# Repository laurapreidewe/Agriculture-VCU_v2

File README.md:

# Agricultural VCU V2

Vehicle control unit PCB for agricultural robots and machinery, built around the Nuvoton M467HJHAN microcontroller. V2 provides Ethernet, CAN, UART, ADC/DAC, PWM, and six relay channels.

The project was originally designed in **KiCad 8** and has been updated to **KiCad 10**. The current schematic and PCB files identify KiCad 10.0 as their generator.

**Known issue:** the relay circuit requires rework because pins **3 and 4** are swapped in the optocoupler footprint. Refer to the [PCB Test Report Rev. A](docs/references/pcb-test-report-rev-a.pdf) for rework details.

## Board overview

The photograph shows the assembled board with relay rework wiring.

## Hardware

| Item | V2 design |
| --- | --- |
| MCU | Nuvoton M467HJHAN, Arm Cortex-M4, LQFP176 |
| Power | 12 V input, external 12 V to 5 V buck module, TPS79533 3.3 V regulator |
| Input protection | Fuse, power switch, and unidirectional TVS diode |
| Ethernet | RTL8201FI PHY, RMII connection to the MCU, magnetics, and RJ45 connector |
| CAN | Two interfaces using external MCP2551 transceiver modules |
| UART | UART0 and UART2 connectors |
| Analogue interfaces | Two ADC inputs with 5 V to 3.3 V scaling and two DAC output channels |
| PWM | Two outputs, BPWM0_CH0 and BPWM1_CH0, with BSS138 level shifting |
| Relays | Six 12 V SPDT channels with optocoupler-based drivers; rework required |
| Expansion and debug | Four 2×20 GPIO sockets and a Nu-Link SWD header |
| Storage | External SPI flash; the V1 SD-card module connector was removed |
| PCB | Four layers, 176.53 × 184.15 mm, 2 mm thick |
| Fabrication limits | 0.1 mm minimum track width/spacing and 0.2 mm minimum hole diameter |

Connector pinouts, switches, LEDs, and test points are listed in the [user manual](docs/references/user-manual.pdf).

## Project files and KiCad setup

Open [UGV Control Unit.kicad_pro](UGV%20Control%20Unit.kicad_pro) with KiCad 10 to work with the current project.

| File | Contents |
| --- | --- |
| [UGV Control Unit.kicad_sch](UGV%20Control%20Unit.kicad_sch) | Root schematic |
| [UGVPower.kicad_sch](UGVPower.kicad_sch) | Power supply |
| [UGVMCU.kicad_sch](UGVMCU.kicad_sch) | MCU, clocks, debug, USB, and flash |
| [UGVGPIO.kicad_sch](UGVGPIO.kicad_sch) | Relays and external interfaces |
| [UGVEthernet.kicad_sch](UGVEthernet.kicad_sch) | Ethernet circuitry |
| [UGV Control Unit.kicad_pcb](UGV%20Control%20Unit.kicad_pcb) | PCB layout |
| [bom/ibom.html](bom/ibom.html) | Interactive BOM and component placement |
| [UGVPCBGerber.zip](UGVPCBGerber.zip) | Existing Gerbers and manufacturing data |
| [UGV Control Unit-odb.zip](UGV%20Control%20Unit-odb.zip) | Existing ODB++ export |
| [Top placement](UGV%20Control%20Unit-top.pos) / [bottom placement](UGV%20Control%20Unit-bottom.pos) | Component position files |
| [3D model.zip](3D%20model.zip) | Complete board STEP model |

The design references custom symbol/footprint libraries, including `MCU_Nuvoton_M467`, `TPS79533DCQ`, and `DESD5V0U1BA_7`. Configure the required libraries when editing or updating components. Some PCB 3D-model paths still use `${KICAD8_3DMODEL_DIR}`; check those paths in KiCad 10 if individual component models are missing. The STEP archive contains the complete board model.

## Changes from V1 to V2

The [Version Control Report](docs/references/version-control-report.pdf) documents the hardware changes from V1 (February 2025) to V2 (January 2026). This hardware revision history is separate from the KiCad 8-to-10 software migration.

| Area | V1 | V2 |
| --- | --- | --- |
| MCU | STM32F446RE, LQFP64 | Nuvoton M467HJHAN, LQFP176 |
| Clocks | 8.192 MHz external crystal; external RTC clock unused | 12 MHz external crystal and external RTC clock |
| Power input | Four-pin connector for 12 V, 72 V, and grounds | Two-pin 12 V/GND connector; added TVS protection |
| MCU supply | VCAP routing mistake required a manual trace cut | LDO_CAP pins kept separate from the 3.3 V rail |
| Decoupling | 0402 capacitors | 0603 capacitors |
| GPIO expansion | One 2×13 and three 2×12 sockets, with 3.3 V and 5 V power pins | Four 2×20 sockets, with 3.3 V power pins |
| Debug | STM32 SWD and boot-jumper circuitry | M467 SWD on PF.0/PF.1 with external pull-ups; simplified boot circuitry |
| Ethernet | Unused | Added PHY, magnetics, and RJ45 interface |
| Relays | 12 relays, BJT-based drivers, D-sub/terminal-block connections | Six SPDT relays, optocoupler-based drivers, individual terminal blocks |
| Interfaces | ADC, DAC, CAN, one UART, and SD-card module connector | Retained ADC/DAC/CAN; two UARTs and two PWM outputs; removed SD-card module connector |
| Storage and USB | No external flash; USB shield directly grounded | Added SPI flash; USB shield connected through a ferrite bead |
| Layout | 180 × 180 mm; components on the top layer | 176.53 × 184.15 mm; some Ethernet components on the bottom layer, edge connectors, and teardrops at small vias |

## Reference documents

| Source | Purpose |
| --- | --- |
| [Presentation1.pptx](docs/references/Presentation1.pptx) | Original annotated board overview, rendered above as a PNG |
| [Agricultural VCU V2 User Manual](docs/references/user-manual.pdf) | Pin assignments, connectors, switches, LEDs, test points, and schematics |
| [Agricultural VCU V2 Testing Protocol](docs/references/testing-protocol.pdf) | Assembly and laboratory test procedures |
| [Agricultural VCU v2 PCB Test Report Rev. A](docs/references/pcb-test-report-rev-a.pdf) | PCB test record and relay rework details |
| [Agricultural VCU V2 Version Control Report](docs/references/version-control-report.pdf) | Changes from hardware V1 to V2 |
| [20260810_Rai.pptx](docs/references/20260810_Rai.pptx) | V2 evaluation list; original location: `season 2/projects/presentation/20260810_Rai.pptx` |

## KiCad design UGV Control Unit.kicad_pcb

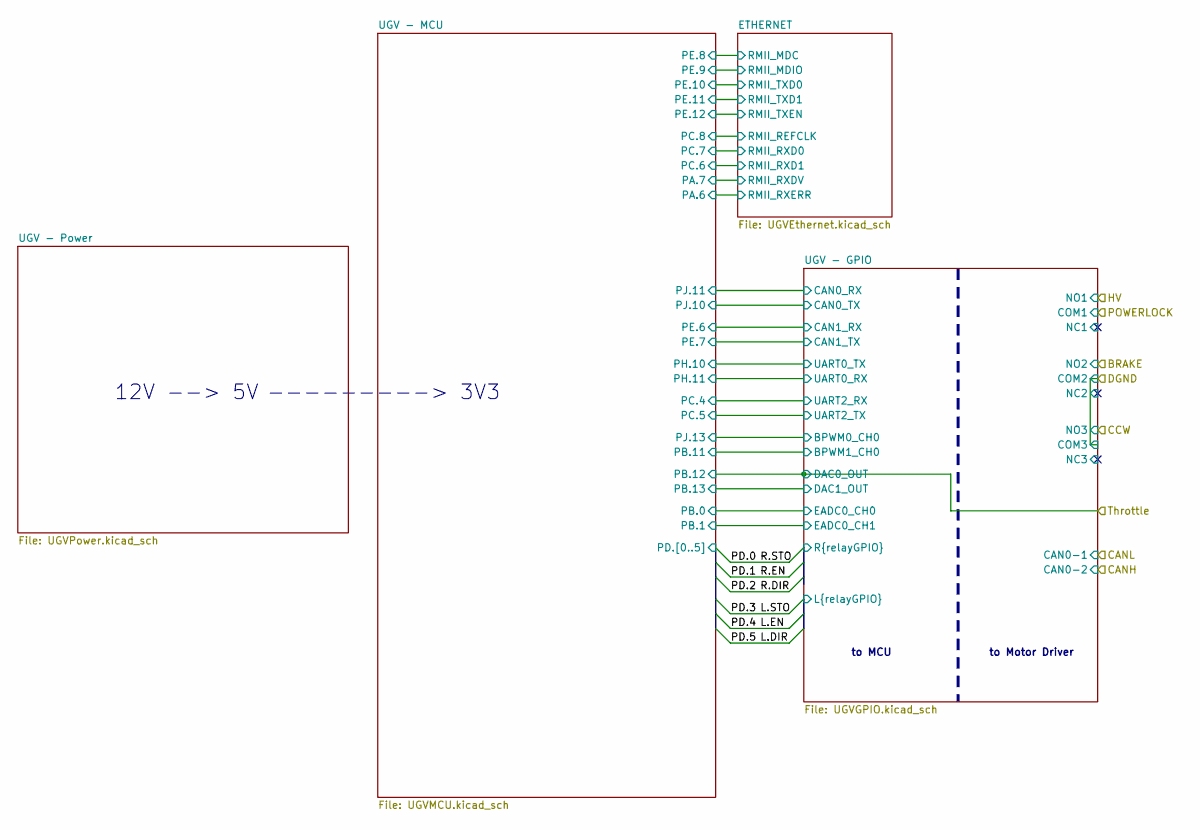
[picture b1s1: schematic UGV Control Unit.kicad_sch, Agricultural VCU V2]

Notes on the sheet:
to MCU
to Motor Driver
12V --> 5V
---------> 3V3

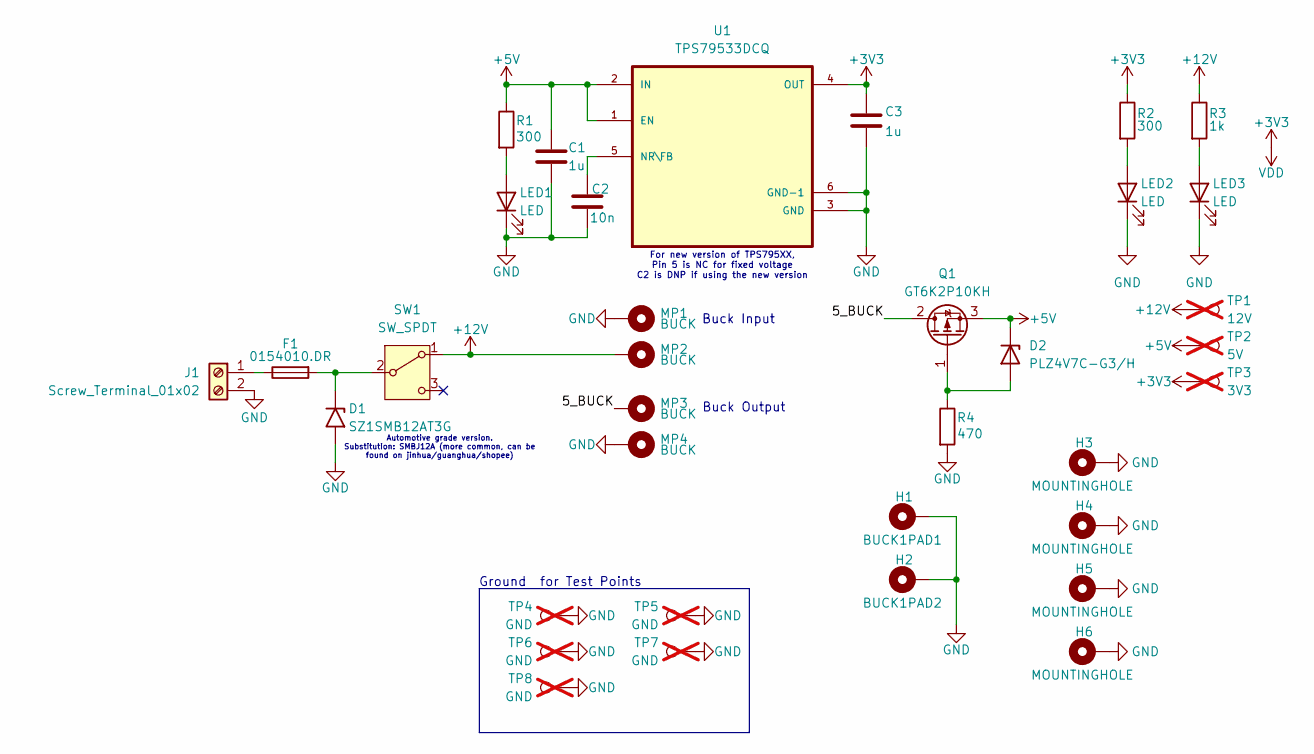
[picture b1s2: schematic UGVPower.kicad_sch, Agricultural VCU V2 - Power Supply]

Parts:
C1, C3: 1u; C_0603_1608Metric_Pad1.08x0.95mm_HandSolder; MANUFACTURER_PART_NUMBER 0603YC105JAT2A
C2: 10n; C_0603_1608Metric_Pad1.08x0.95mm_HandSolder; MANUFACTURER_PART_NUMBER KGM15AR51E103KT
D1: SZ1SMB12AT3G; D_SMB_Handsoldering; MANUFACTURER_PART_NUMBER SZ1SMB12AT3G
D2: PLZ4V7C-G3/H; CR_PLZ5V1C_VIS-L; MANUFACTURER_PART_NUMBER PLZ4V7C
F1: 0154010.DR; Fuseholder_Littelfuse_Nano2_154x; MANUFACTURER_PART_NUMBER 0154010.DR
H1: BUCK1PAD1; MountingHole_3.2mm_M3_Pad_TopBottom
H2: BUCK1PAD2; MountingHole_3.2mm_M3_Pad_TopBottom
H3, H4, H5, H6: MOUNTINGHOLE; MountingHole_3.2mm_M3_Pad_Via
J1: Screw_Terminal_01x02; TerminalBlock_TE_NC6-P107-02_1x02_P9.53mm; MANUFACTURER_PART_NUMBER 1437664-4
LED1, LED2, LED3: LED; LED_0603_1608Metric_Pad1.05x0.95mm_HandSolder; MANUFACTURER_PART_NUMBER 150060SS75003
MP1, MP2, MP3, MP4: BUCK; MountingHole_4.3mm_M4_Pad_TopBottom; MANUFACTURER_PART_NUMBER 24885
Q1: GT6K2P10KH; TO-252-2; MANUFACTURER_PART_NUMBER GT6K2P10KH
R1, R2: 300; R_0603_1608Metric_Pad0.98x0.95mm_HandSolder; MANUFACTURER_PART_NUMBER RT0603BRD07300RL
R3: 1k; R_0603_1608Metric_Pad0.98x0.95mm_HandSolder; MANUFACTURER_PART_NUMBER RT0603FRE131KL
R4: 470; R_0603_1608Metric_Pad0.98x0.95mm_HandSolder; MANUFACTURER_PART_NUMBER RT0603FRE07470RL
SW1: SW_SPDT; SW_500SSP1S1M2REA; MANUFACTURER_PART_NUMBER 500SSP1S1M2REA
TP1: 12V; TestPoint_Pad_D1.0mm; not fitted
TP2: 5V; TestPoint_Pad_D1.0mm; not fitted
TP3: 3V3; TestPoint_Pad_D1.0mm; not fitted
TP4, TP5, TP6, TP7, TP8: GND; PinHeader_1x01_P2.54mm_Vertical; not fitted
U1: TPS79533DCQ; SOT127P706X180-6N; MANUFACTURER_PART_NUMBER TPS79533DCQ

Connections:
+12V: MP2.1, R3.1, SW1.1 (A), TP1.1; also elsewhere on the board
/UGV - Power/5_BUCK: MP3.1, Q1.2 (D)
GND: C1.2, C2.2, C3.2, D1.2 (A2), H1.1, H2.1, H3.1, H4.1, H5.1, H6.1, J1.2, LED1.1 (K), LED2.1 (K), LED3.1 (K), MP1.1, MP4.1, R4.2, TP4.1, TP5.1, TP6.1, TP7.1, TP8.1, U1.3 (GND), U1.6 (GND-1); also elsewhere on the board
unnamed: D1.1 (A1), F1.2, SW1.2 (B)
unnamed: D2.2 (A), Q1.1 (G), R4.1
unnamed: F1.1, J1.1
unnamed: LED1.2 (A), R1.2
unnamed: LED2.2 (A), R2.2
unnamed: LED3.2 (A), R3.2
unnamed: C2.1, U1.5 (NR\FB)

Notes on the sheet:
Automotive grade version. Substitution: SMBJ12A (more common, can be found on jinhua/guanghua/shopee)
Ground for Test Points
Buck Input
For new version of TPS795XX, Pin 5 is NC for fixed voltage C2 is DNP if using the new version
Buck Output

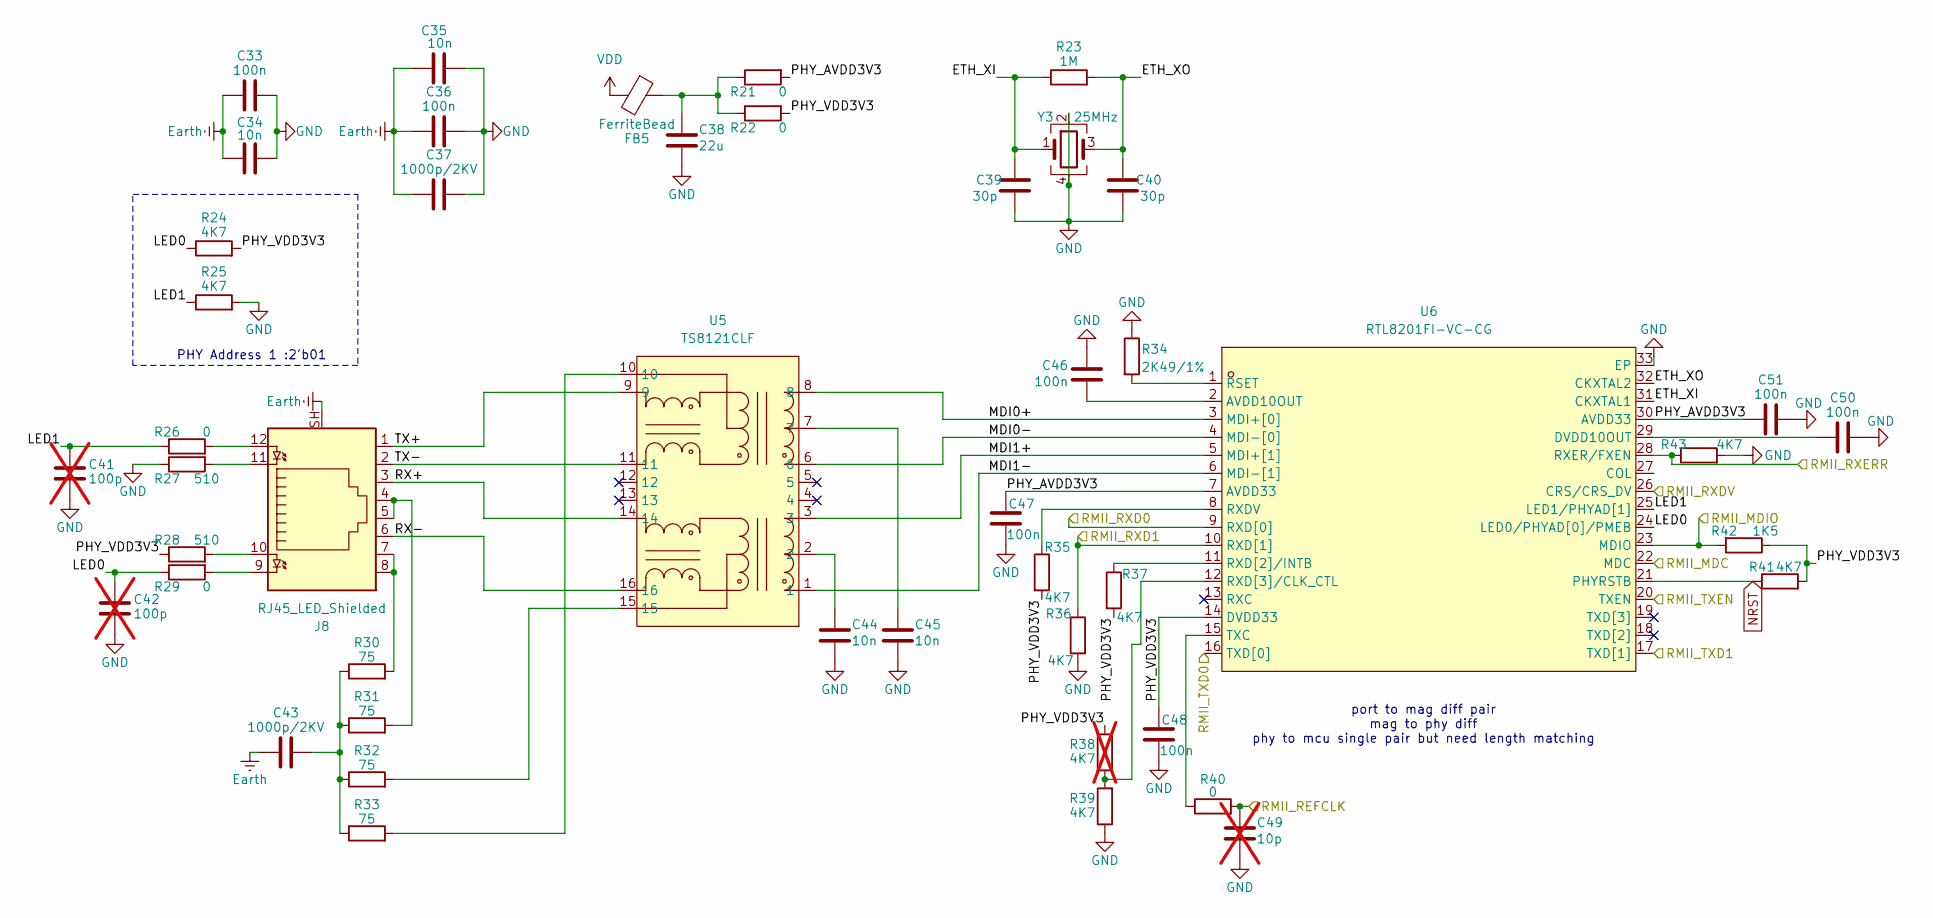
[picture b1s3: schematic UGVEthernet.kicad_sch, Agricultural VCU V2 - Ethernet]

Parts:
C33, C36, C46, C47, C48, C50, C51: 100n; C_0603_1608Metric_Pad1.08x0.95mm_HandSolder; MANUFACTURER_PART_NUMBER KGM15BR71H104KT
C34, C35, C44, C45: 10n; C_0603_1608Metric_Pad1.08x0.95mm_HandSolder; MANUFACTURER_PART_NUMBER KGM15AR51E103KT
C37, C43: 1000p/2KV; C_1206_3216Metric_Pad1.33x1.80mm_HandSolder; MANUFACTURER_PART_NUMBER CC1206JKX7RDBB102
C38: 22u; C_0603_1608Metric_Pad1.08x0.95mm_HandSolder; MANUFACTURER_PART_NUMBER GRM188R61A226ME15D
C39, C40: 30p; C_0603_1608Metric_Pad1.08x0.95mm_HandSolder; MANUFACTURER_PART_NUMBER 06035A300JAT2A
C41, C42: 100p; C_0603_1608Metric_Pad1.08x0.95mm_HandSolder; MANUFACTURER_PART_NUMBER KGM15ACG1H101FT; not fitted
C49: 10p; C_0603_1608Metric_Pad1.08x0.95mm_HandSolder; MANUFACTURER_PART_NUMBER CC0603JRNPO9BN100; not fitted
FB5: FerriteBead; L_0603_1608Metric_Pad1.05x0.95mm_HandSolder; MANUFACTURER_PART_NUMBER BLM18KG300TN1D
J8: RJ45_LED_Shielded; RJ45_Amphenol_RJHSE538X; MANUFACTURER_PART_NUMBER RJHSE5381
R21, R22, R26, R29, R40: 0; R_0603_1608Metric_Pad0.98x0.95mm_HandSolder; MANUFACTURER_PART_NUMBER RC0603JR-070RL
R23: 1M; R_0603_1608Metric_Pad0.98x0.95mm_HandSolder; MANUFACTURER_PART_NUMBER RC0603FR-101ML
R24, R25, R35, R36, R37, R39, R41, R43: 4K7; R_0603_1608Metric_Pad0.98x0.95mm_HandSolder; MANUFACTURER_PART_NUMBER RC0603FR-134K7L
R27, R28: 510; R_0603_1608Metric_Pad0.98x0.95mm_HandSolder; MANUFACTURER_PART_NUMBER RT0603BRD07510RL
R30, R31, R32, R33: 75; R_0603_1608Metric_Pad0.98x0.95mm_HandSolder; MANUFACTURER_PART_NUMBER RC0603FR-0775RL
R34: 2K49/1%; R_0603_1608Metric_Pad0.98x0.95mm_HandSolder; MANUFACTURER_PART_NUMBER RC0603FR-072K49L
R38: 4K7; R_0603_1608Metric_Pad0.98x0.95mm_HandSolder; MANUFACTURER_PART_NUMBER RC0603FR-134K7L; not fitted
R42: 1K5; R_0603_1608Metric_Pad0.98x0.95mm_HandSolder; MANUFACTURER_PART_NUMBER RT0603FRE071K5L
U5: TS8121CLF; SOP-16_7.0x13.0mm_P1.27mm; MANUFACTURER_PART_NUMBER TS8121CLF; LCSC Part C2839017
U6: RTL8201FI-VC-CG; QFN-32-1EP_5x5mm_P0.5mm_EP3.3x3.3mm_ThermalVias; MANUFACTURER_PART_NUMBER RTL8201FI-VC-CG; LCSC Part C2763557
Y3: 25MHz; Crystal_SMD_SeikoEpson_TSX3225-4Pin_3.2x2.5mm_HandSoldering; MANUFACTURER_PART_NUMBER TSX-3225 25.0000MF10P-C0

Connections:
/ETHERNET/ETH_XI: C39.1, R23.1, U6.31 (CKXTAL1), Y3.1
/ETHERNET/ETH_XO: C40.1, R23.2, U6.32 (CKXTAL2), Y3.3
/ETHERNET/LED0: C42.1, R24.1, R29.1, U6.24 (LED0/PHYAD[0]/PMEB)
/ETHERNET/LED1: C41.1, R25.1, R26.1, U6.25 (LED1/PHYAD[1])
/ETHERNET/MDI0+: U5.8, U6.3 (MDI+[0])
/ETHERNET/MDI0-: U5.6, U6.4 (MDI-[0])
/ETHERNET/MDI1+: U5.3, U6.5 (MDI+[1])
/ETHERNET/MDI1-: U5.1, U6.6 (MDI-[1])
/ETHERNET/PHY_AVDD3V3: C47.1, C51.2, R21.2, U6.7 (AVDD33), U6.30 (AVDD33)
/ETHERNET/PHY_VDD3V3: C48.1, R22.2, R24.2, R28.1, R35.2, R37.2, R38.2, R41.2, R42.1, U6.14 (DVDD33)
/ETHERNET/RX+: J8.3, U5.14
/ETHERNET/RX-: J8.6, U5.16
/ETHERNET/TX+: J8.1, U5.9
/ETHERNET/TX-: J8.2, U5.11
/UGV - MCU/PA.6: R43.1, U6.28 (RXER/FXEN); also elsewhere on the board
/UGV - MCU/PA.7: U6.26 (CRS/CRS_DV); also elsewhere on the board
/UGV - MCU/PC.6: R36.1, U6.10 (RXD[1]); also elsewhere on the board
/UGV - MCU/PC.7: U6.9 (RXD[0]); also elsewhere on the board
/UGV - MCU/PC.8: C49.1, R40.2; also elsewhere on the board
/UGV - MCU/PE.8: U6.22 (MDC); also elsewhere on the board
/UGV - MCU/PE.9: R42.2, U6.23 (MDIO); also elsewhere on the board
/UGV - MCU/PE.10: U6.16 (TXD[0]); also elsewhere on the board
/UGV - MCU/PE.11: U6.17 (TXD[1]); also elsewhere on the board
/UGV - MCU/PE.12: U6.20 (TXEN); also elsewhere on the board
Earth: C33.1, C34.2, C35.1, C36.2, C37.1, C43.1, J8.SH
GND: C33.2, C34.1, C35.2, C36.1, C37.2, C38.2, C39.2, C40.2, C41.2, C42.2, C44.2, C45.2, C46.1, C47.2, C48.2, C49.2, C50.1, C51.1, R25.2, R27.1, R34.1, R36.2, R39.1, R43.2, U6.33 (EP), Y3.2, Y3.4; also elsewhere on the board
NRST: R41.1, U6.21 (PHYRSTB); also elsewhere on the board
unnamed: C38.1, FB5.1, R21.1, R22.1
unnamed: C43.2, R30.1, R31.1, R32.1, R33.1
unnamed: C44.1, U5.2
unnamed: C45.1, U5.7
unnamed: J8.4, J8.5, R31.2
unnamed: J8.7, J8.8, R30.2
unnamed: J8.9, R29.2
unnamed: J8.10, R28.2
unnamed: J8.11, R27.2
unnamed: J8.12, R26.2
unnamed: R32.2, U5.15
unnamed: R33.2, U5.10
unnamed: C46.2, U6.2 (AVDD10OUT)
unnamed: C50.2, U6.29 (DVDD10OUT)
unnamed: R34.2, U6.1 (RSET)
unnamed: R35.1, U6.8 (RXDV)
unnamed: R37.1, U6.11 (RXD[2]/INTB)
unnamed: R38.1, R39.2, U6.12 (RXD[3]/CLK_CTL)
unnamed: R40.1, U6.15 (TXC)

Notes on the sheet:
port to mag diff pair mag to phy diff phy to mcu single pair but need length matching
PHY Address 1 :2'b01

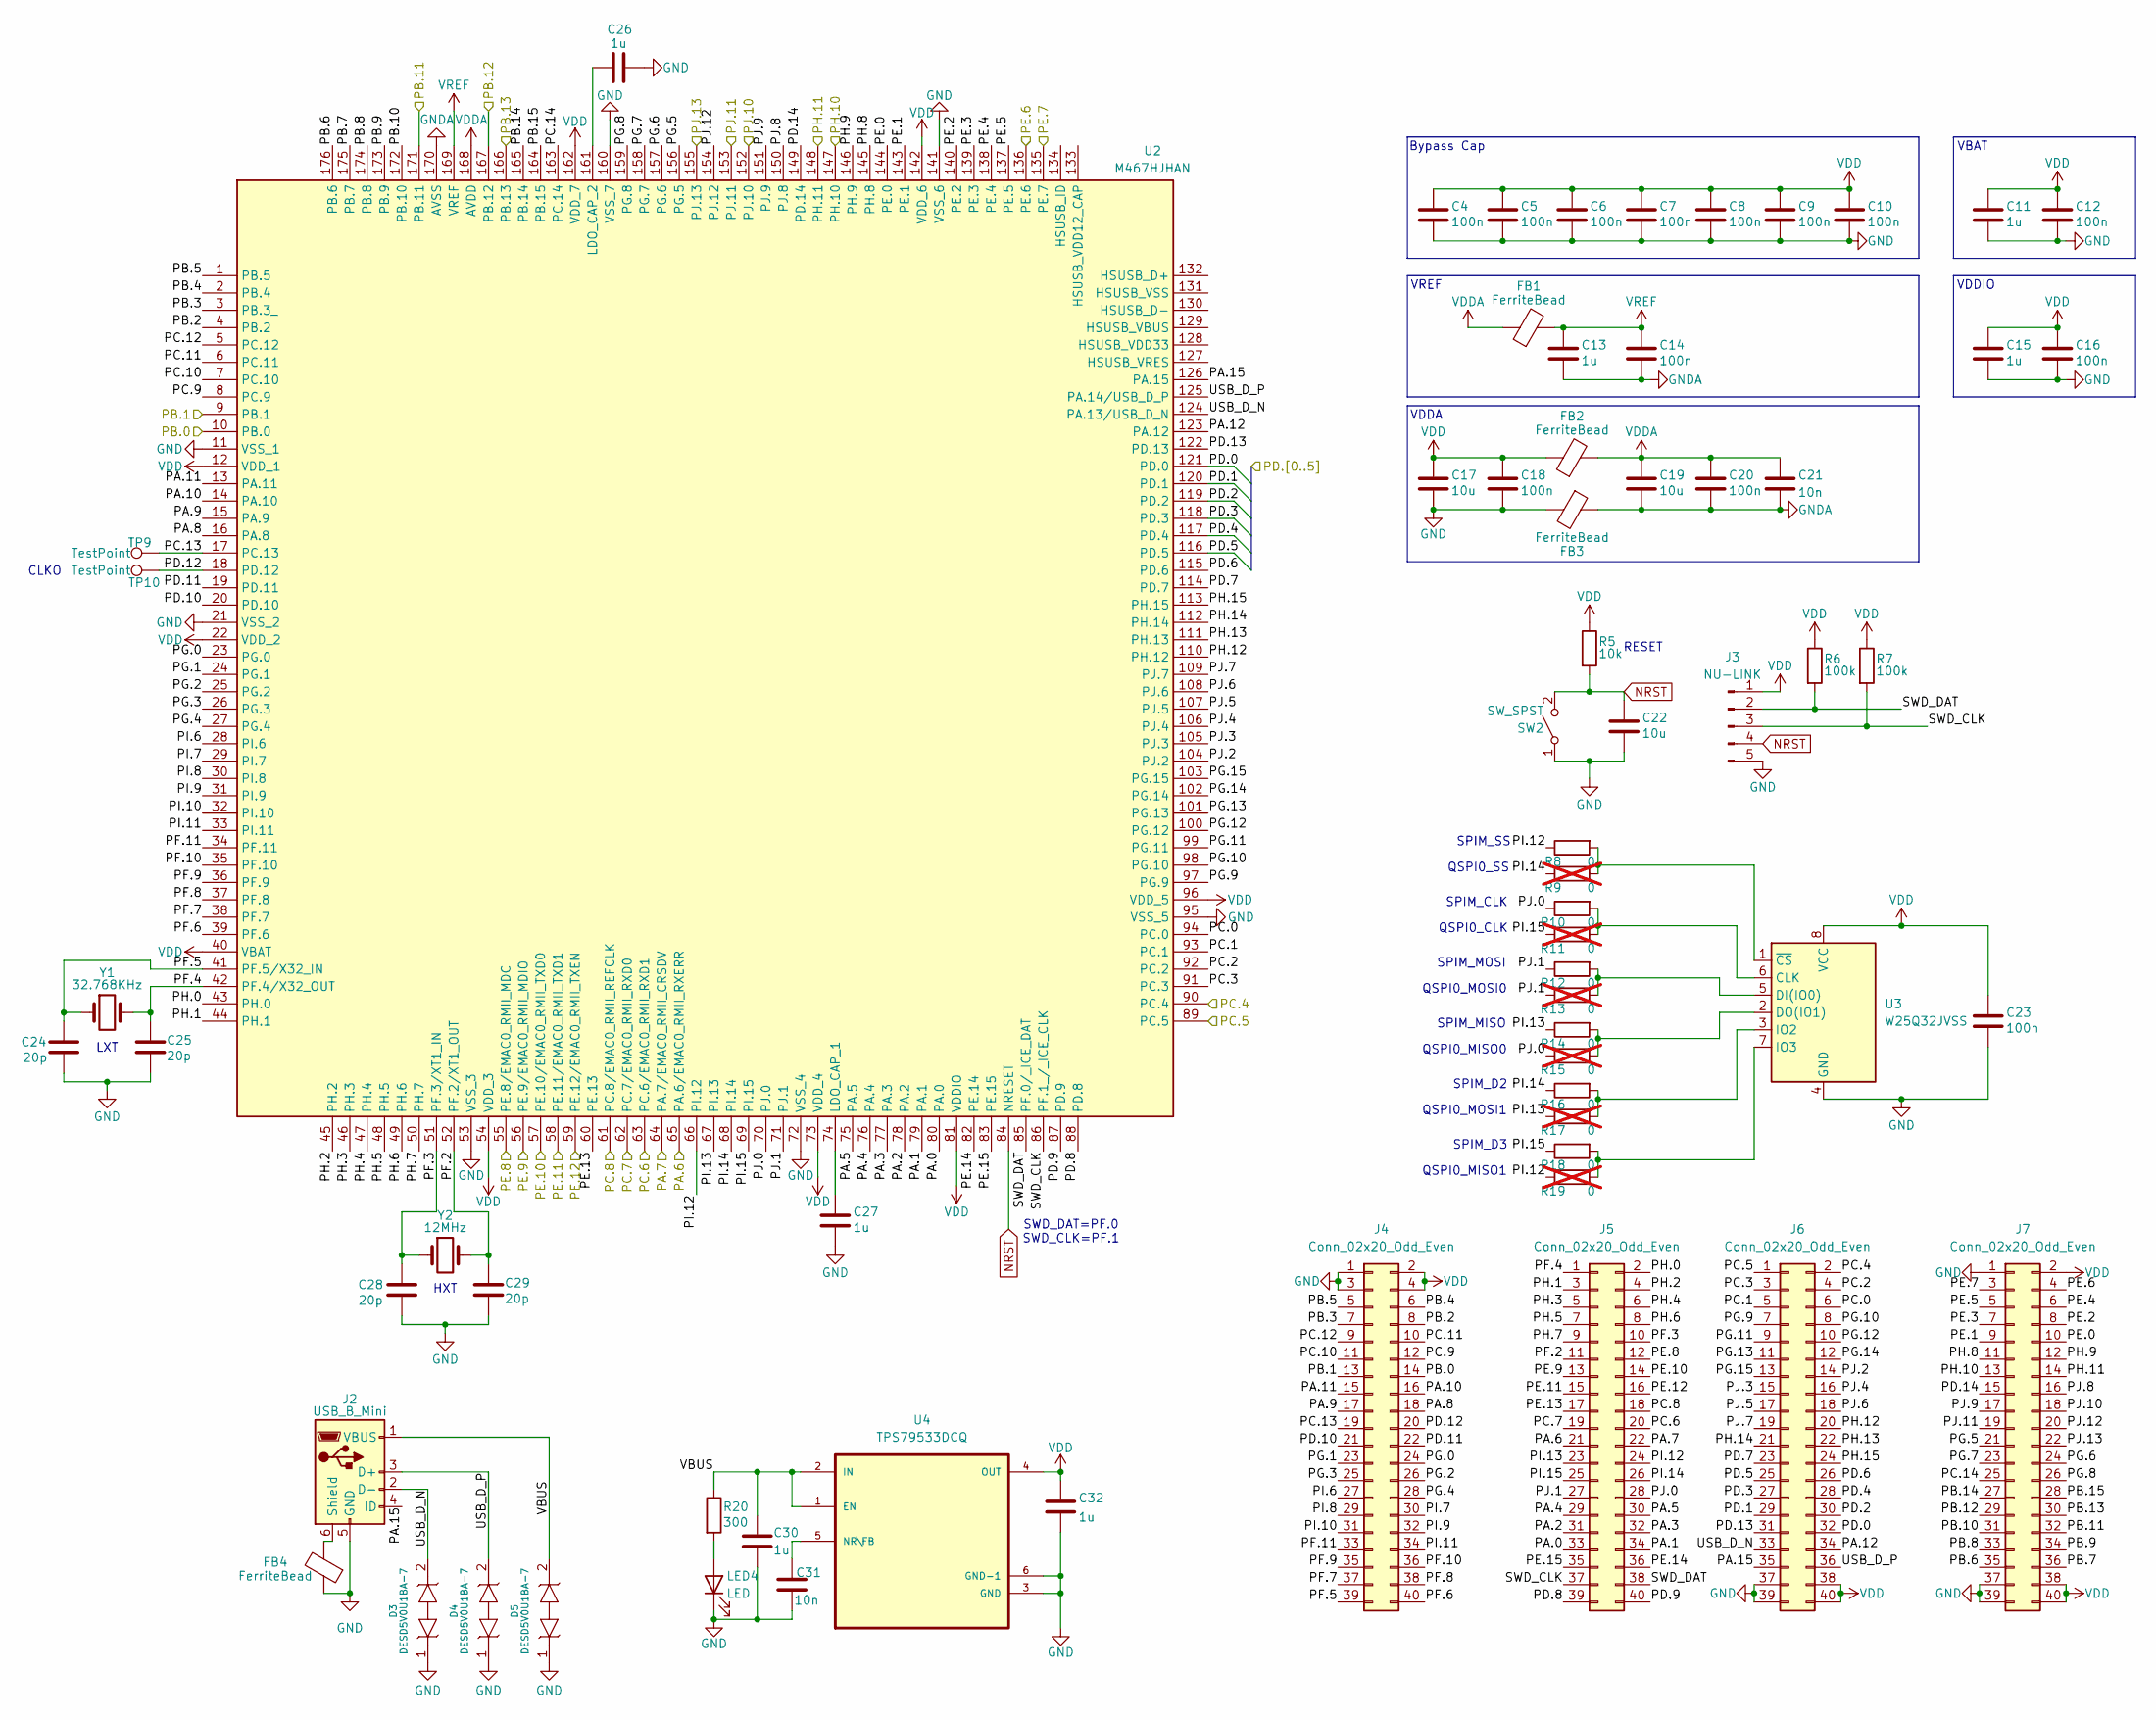
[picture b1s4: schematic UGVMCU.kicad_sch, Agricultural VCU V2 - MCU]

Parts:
C4, C5, C6, C7, C8, C9, C10, C12, C14, C16, C18, C20, C23: 100n; C_0603_1608Metric_Pad1.08x0.95mm_HandSolder; MANUFACTURER_PART_NUMBER KGM15BR71H104KT
C11, C13, C15, C26, C27, C30, C32: 1u; C_0603_1608Metric_Pad1.08x0.95mm_HandSolder; MANUFACTURER_PART_NUMBER 0603YC105JAT2A
C17, C19, C22: 10u; C_0603_1608Metric_Pad1.08x0.95mm_HandSolder; MANUFACTURER_PART_NUMBER GRM188D71A106KA73D
C21, C31: 10n; C_0603_1608Metric_Pad1.08x0.95mm_HandSolder; MANUFACTURER_PART_NUMBER KGM15AR51E103KT
C24, C25, C28, C29: 20p; C_0603_1608Metric_Pad1.08x0.95mm_HandSolder; MANUFACTURER_PART_NUMBER 06035A200JAT2A
D3, D4, D5: DESD5V0U1BA-7; SOD323-L_DIO; MANUFACTURER_PART_NUMBER DESD5V0U1BA
FB1, FB2, FB3, FB4: FerriteBead; L_0603_1608Metric_Pad1.05x0.95mm_HandSolder; MANUFACTURER_PART_NUMBER BLM18KG300TN1D
J2: USB_B_Mini; USB_Mini-B_Wuerth_65100516121_Horizontal; MANUFACTURER_PART_NUMBER 1734035-3
J3: NU-LINK; PinHeader_1x05_P2.54mm_Vertical; MANUFACTURER_PART_NUMBER PH1-05-UA
J4, J5, J6, J7: Conn_02x20_Odd_Even; PinSocket_2x20_P2.54mm_Vertical
LED4: LED; LED_0603_1608Metric_Pad1.05x0.95mm_HandSolder; MANUFACTURER_PART_NUMBER 150060SS75003
R5: 10k; R_0603_1608Metric_Pad0.98x0.95mm_HandSolder; MANUFACTURER_PART_NUMBER RT0603FRE0710KL
R6, R7: 100k; R_0603_1608Metric_Pad0.98x0.95mm_HandSolder; MANUFACTURER_PART_NUMBER RT0603BRE07100KL
R8, R10, R12, R14, R16, R18: 0; R_0603_1608Metric_Pad0.98x0.95mm_HandSolder; MANUFACTURER_PART_NUMBER RC0603JR-070RL
R9, R11, R13, R15, R17, R19: 0; R_0603_1608Metric_Pad0.98x0.95mm_HandSolder; MANUFACTURER_PART_NUMBER RC0603JR-070RL; not fitted
R20: 300; R_0603_1608Metric_Pad0.98x0.95mm_HandSolder; MANUFACTURER_PART_NUMBER RT0603BRD07300RL
SW2: SW_SPST; SW_PUSH_6mm; MANUFACTURER_PART_NUMBER TL1105F160QWITHSTRAIGHT
TP9, TP10: TestPoint; PinHeader_1x01_P2.54mm_Vertical
U2: M467HJHAN; LQFP-176_24x24mm_P0.5mm; Manufacturer_Part_Number M467HJHAN
U3: W25Q32JVSS; SOIC-8_5.23x5.23mm_P1.27mm; MANUFACTURER_PART_NUMBER W25Q32JVSSIQ
U4: TPS79533DCQ; SOT127P706X180-6N; MANUFACTURER_PART_NUMBER TPS79533DCQ
Y1: 32.768KHz; Crystal_SMD_EuroQuartz_EQ161-2Pin_3.2x1.5mm_HandSoldering; MANUFACTURER_PART_NUMBER ABS07-32.768KHZ-T
Y2: 12MHz; Crystal_HC49-4H_Vertical

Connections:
/UGV - GPIO/CAN0_RX: J7.19, U2.153 (PJ.11); also elsewhere on the board
/UGV - GPIO/CAN0_TX: J7.18, U2.152 (PJ.10); also elsewhere on the board
/UGV - GPIO/CAN1_RX: J7.4, U2.136 (PE.6); also elsewhere on the board
/UGV - GPIO/CAN1_TX: J7.3, U2.135 (PE.7); also elsewhere on the board
/UGV - GPIO/L.DIR: J6.25, U2.116 (PD.5); also elsewhere on the board
/UGV - GPIO/L.EN: J6.28, U2.117 (PD.4); also elsewhere on the board
/UGV - GPIO/L.STO: J6.27, U2.118 (PD.3); also elsewhere on the board
/UGV - GPIO/UART0_RX: J7.14, U2.148 (PH.11); also elsewhere on the board
/UGV - GPIO/UART0_TX: J7.13, U2.147 (PH.10); also elsewhere on the board
/UGV - GPIO/UART2_RX: J6.2, U2.90 (PC.4); also elsewhere on the board
/UGV - GPIO/UART2_TX: J6.1, U2.89 (PC.5); also elsewhere on the board
/UGV - MCU/PA.0: J5.33, U2.80 (PA.0)
/UGV - MCU/PA.1: J5.34, U2.79 (PA.1)
/UGV - MCU/PA.2: J5.31, U2.78 (PA.2)
/UGV - MCU/PA.3: J5.32, U2.77 (PA.3)
/UGV - MCU/PA.4: J5.29, U2.76 (PA.4)
/UGV - MCU/PA.5: J5.30, U2.75 (PA.5)
/UGV - MCU/PA.6: J5.21, U2.65 (PA.6/EMAC0_RMII_RXERR); also elsewhere on the board
/UGV - MCU/PA.7: J5.22, U2.64 (PA.7/EMAC0_RMII_CRSDV); also elsewhere on the board
/UGV - MCU/PA.8: J4.18, U2.16 (PA.8)
/UGV - MCU/PA.9: J4.17, U2.15 (PA.9)
/UGV - MCU/PA.10: J4.16, U2.14 (PA.10)
/UGV - MCU/PA.11: J4.15, U2.13 (PA.11)
/UGV - MCU/PA.12: J6.34, U2.123 (PA.12)
/UGV - MCU/PA.15: J2.4 (ID), J6.35, U2.126 (PA.15)
/UGV - MCU/PB.0: J4.14, U2.10 (PB.0); also elsewhere on the board
/UGV - MCU/PB.1: J4.13, U2.9 (PB.1); also elsewhere on the board
/UGV - MCU/PB.2: J4.8, U2.4 (PB.2)
/UGV - MCU/PB.3: J4.7, U2.3 (PB.3_)
/UGV - MCU/PB.4: J4.6, U2.2 (PB.4)
/UGV - MCU/PB.5: J4.5, U2.1 (PB.5)
/UGV - MCU/PB.6: J7.35, U2.176 (PB.6)
/UGV - MCU/PB.7: J7.36, U2.175 (PB.7)
/UGV - MCU/PB.8: J7.33, U2.174 (PB.8)
/UGV - MCU/PB.9: J7.34, U2.173 (PB.9)
/UGV - MCU/PB.10: J7.31, U2.172 (PB.10)
/UGV - MCU/PB.11: J7.32, U2.171 (PB.11); also elsewhere on the board
/UGV - MCU/PB.12: J7.29, U2.167 (PB.12); also elsewhere on the board
/UGV - MCU/PB.13: J7.30, U2.166 (PB.13); also elsewhere on the board
/UGV - MCU/PB.14: J7.27, U2.165 (PB.14)
/UGV - MCU/PB.15: J7.28, U2.164 (PB.15)
/UGV - MCU/PC.0: J6.6, U2.94 (PC.0)
/UGV - MCU/PC.1: J6.5, U2.93 (PC.1)
/UGV - MCU/PC.2: J6.4, U2.92 (PC.2)
/UGV - MCU/PC.3: J6.3, U2.91 (PC.3)
/UGV - MCU/PC.6: J5.20, U2.63 (PC.6/EMAC0_RMII_RXD1); also elsewhere on the board
/UGV - MCU/PC.7: J5.19, U2.62 (PC.7/EMAC0_RMII_RXD0); also elsewhere on the board
/UGV - MCU/PC.8: J5.18, U2.61 (PC.8/EMAC0_RMII_REFCLK); also elsewhere on the board
/UGV - MCU/PC.9: J4.12, U2.8 (PC.9)
/UGV - MCU/PC.10: J4.11, U2.7 (PC.10)
/UGV - MCU/PC.11: J4.10, U2.6 (PC.11)
/UGV - MCU/PC.12: J4.9, U2.5 (PC.12)
/UGV - MCU/PC.13: J4.19, TP9.1, U2.17 (PC.13)
/UGV - MCU/PC.14: J7.25, U2.163 (PC.14)
/UGV - MCU/PD.0: J6.32, U2.121 (PD.0); also elsewhere on the board
/UGV - MCU/PD.1: J6.29, U2.120 (PD.1); also elsewhere on the board
/UGV - MCU/PD.2: J6.30, U2.119 (PD.2); also elsewhere on the board
/UGV - MCU/PD.6: J6.26, U2.115 (PD.6)
/UGV - MCU/PD.7: J6.23, U2.114 (PD.7)
/UGV - MCU/PD.8: J5.39, U2.88 (PD.8)
/UGV - MCU/PD.9: J5.40, U2.87 (PD.9)
/UGV - MCU/PD.10: J4.21, U2.20 (PD.10)
/UGV - MCU/PD.11: J4.22, U2.19 (PD.11)
/UGV - MCU/PD.12: J4.20, TP10.1, U2.18 (PD.12)
/UGV - MCU/PD.13: J6.31, U2.122 (PD.13)
/UGV - MCU/PD.14: J7.15, U2.149 (PD.14)
/UGV - MCU/PE.0: J7.10, U2.144 (PE.0)
/UGV - MCU/PE.1: J7.9, U2.143 (PE.1)
/UGV - MCU/PE.2: J7.8, U2.140 (PE.2)
/UGV - MCU/PE.3: J7.7, U2.139 (PE.3)
/UGV - MCU/PE.4: J7.6, U2.138 (PE.4)
/UGV - MCU/PE.5: J7.5, U2.137 (PE.5)
/UGV - MCU/PE.8: J5.12, U2.55 (PE.8/EMAC0_RMII_MDC); also elsewhere on the board
/UGV - MCU/PE.9: J5.13, U2.56 (PE.9/EMAC0_RMII_MDIO); also elsewhere on the board
/UGV - MCU/PE.10: J5.14, U2.57 (PE.10/EMAC0_RMII_TXD0); also elsewhere on the board
/UGV - MCU/PE.11: J5.15, U2.58 (PE.11/EMAC0_RMII_TXD1); also elsewhere on the board
/UGV - MCU/PE.12: J5.16, U2.59 (PE.12/EMAC0_RMII_TXEN); also elsewhere on the board
/UGV - MCU/PE.13: J5.17, U2.60 (PE.13)
/UGV - MCU/PE.14: J5.36, U2.82 (PE.14)
/UGV - MCU/PE.15: J5.35, U2.83 (PE.15)
/UGV - MCU/PF.2: C29.1, J5.11, U2.52 (PF.2/XT1_OUT), Y2.2
/UGV - MCU/PF.3: C28.1, J5.10, U2.51 (PF.3/XT1_IN), Y2.1
/UGV - MCU/PF.4: C25.1, J5.1, U2.42 (PF.4/X32_OUT), Y1.2
/UGV - MCU/PF.5: C24.1, J4.39, U2.41 (PF.5/X32_IN), Y1.1
/UGV - MCU/PF.6: J4.40, U2.39 (PF.6)
/UGV - MCU/PF.7: J4.37, U2.38 (PF.7)
/UGV - MCU/PF.8: J4.38, U2.37 (PF.8)
/UGV - MCU/PF.9: J4.35, U2.36 (PF.9)
/UGV - MCU/PF.10: J4.36, U2.35 (PF.10)
/UGV - MCU/PF.11: J4.33, U2.34 (PF.11)
/UGV - MCU/PG.0: J4.24, U2.23 (PG.0)
/UGV - MCU/PG.1: J4.23, U2.24 (PG.1)
/UGV - MCU/PG.2: J4.26, U2.25 (PG.2)
/UGV - MCU/PG.3: J4.25, U2.26 (PG.3)
/UGV - MCU/PG.4: J4.28, U2.27 (PG.4)
/UGV - MCU/PG.5: J7.21, U2.156 (PG.5)
/UGV - MCU/PG.6: J7.24, U2.157 (PG.6)
/UGV - MCU/PG.7: J7.23, U2.158 (PG.7)
/UGV - MCU/PG.8: J7.26, U2.159 (PG.8)
/UGV - MCU/PG.9: J6.7, U2.97 (PG.9)
/UGV - MCU/PG.10: J6.8, U2.98 (PG.10)
/UGV - MCU/PG.11: J6.9, U2.99 (PG.11)
/UGV - MCU/PG.12: J6.10, U2.100 (PG.12)
/UGV - MCU/PG.13: J6.11, U2.101 (PG.13)
/UGV - MCU/PG.14: J6.12, U2.102 (PG.14)
/UGV - MCU/PG.15: J6.13, U2.103 (PG.15)
/UGV - MCU/PH.0: J5.2, U2.43 (PH.0)
/UGV - MCU/PH.1: J5.3, U2.44 (PH.1)
/UGV - MCU/PH.2: J5.4, U2.45 (PH.2)
/UGV - MCU/PH.3: J5.5, U2.46 (PH.3)
/UGV - MCU/PH.4: J5.6, U2.47 (PH.4)
/UGV - MCU/PH.5: J5.7, U2.48 (PH.5)
/UGV - MCU/PH.6: J5.8, U2.49 (PH.6)
/UGV - MCU/PH.7: J5.9, U2.50 (PH.7)
/UGV - MCU/PH.8: J7.11, U2.145 (PH.8)
/UGV - MCU/PH.9: J7.12, U2.146 (PH.9)
/UGV - MCU/PH.12: J6.20, U2.110 (PH.12)
/UGV - MCU/PH.13: J6.22, U2.111 (PH.13)
/UGV - MCU/PH.14: J6.21, U2.112 (PH.14)
/UGV - MCU/PH.15: J6.24, U2.113 (PH.15)
/UGV - MCU/PI.6: J4.27, U2.28 (PI.6)
/UGV - MCU/PI.7: J4.30, U2.29 (PI.7)
/UGV - MCU/PI.8: J4.29, U2.30 (PI.8)
/UGV - MCU/PI.9: J4.32, U2.31 (PI.9)
/UGV - MCU/PI.10: J4.31, U2.32 (PI.10)
/UGV - MCU/PI.11: J4.34, U2.33 (PI.11)
/UGV - MCU/PI.12: J5.24, R8.1, R19.1, U2.66 (PI.12)
/UGV - MCU/PI.13: J5.23, R14.1, R17.1, U2.67 (PI.13)
/UGV - MCU/PI.14: J5.26, R9.1, R16.1, U2.68 (PI.14)
/UGV - MCU/PI.15: J5.25, R11.1, R18.1, U2.69 (PI.15)
/UGV - MCU/PJ.0: J5.28, R10.1, R15.1, U2.70 (PJ.0)
/UGV - MCU/PJ.1: J5.27, R12.1, R13.1, U2.71 (PJ.1)
/UGV - MCU/PJ.2: J6.14, U2.104 (PJ.2)
/UGV - MCU/PJ.3: J6.15, U2.105 (PJ.3)
/UGV - MCU/PJ.4: J6.16, U2.106 (PJ.4)
/UGV - MCU/PJ.5: J6.17, U2.107 (PJ.5)
/UGV - MCU/PJ.6: J6.18, U2.108 (PJ.6)
/UGV - MCU/PJ.7: J6.19, U2.109 (PJ.7)
/UGV - MCU/PJ.8: J7.16, U2.150 (PJ.8)
/UGV - MCU/PJ.9: J7.17, U2.151 (PJ.9)
/UGV - MCU/PJ.12: J7.20, U2.154 (PJ.12)
/UGV - MCU/PJ.13: J7.22, U2.155 (PJ.13); also elsewhere on the board
/UGV - MCU/SWD_CLK: J3.3, J5.37, R7.2, U2.86 (PF.1_/_ICE_CLK)
/UGV - MCU/SWD_DAT: J3.2, J5.38, R6.2, U2.85 (PF.0/_ICE_DAT)
/UGV - MCU/USB_D_N: D3.2, J2.2 (D-), J6.33, U2.124 (PA.13/USB_D_N)
/UGV - MCU/USB_D_P: D4.2, J2.3 (D+), J6.36, U2.125 (PA.14/USB_D_P)
/UGV - MCU/VBUS: C30.1, D5.2, J2.1 (VBUS), R20.1, U4.1 (EN), U4.2 (IN)
GND: C4.2, C5.2, C6.2, C7.2, C8.2, C9.2, C10.2, C11.2, C12.2, C15.2, C16.2, C17.2, C18.2, C22.2, C23.2, C24.2, C25.2, C26.1, C27.2, C28.2, C29.2, C30.2, C31.2, C32.2, D3.1, D4.1, D5.1, FB3.2, FB4.1, J2.5 (GND), J3.5, J4.1, J4.3, J6.37, J6.39, J7.1, J7.37, J7.39, LED4.1 (K), SW2.1 (A), U2.11 (VSS_1), U2.21 (VSS_2), U2.53 (VSS_3), U2.72 (VSS_4), U2.95 (VSS_5), U2.141 (VSS_6), U2.160 (VSS_7), U3.4 (GND), U4.3 (GND), U4.6 (GND-1); also elsewhere on the board
GNDA: C13.2, C14.2, C19.2, C20.2, C21.2, FB3.1, U2.170 (AVSS)
NRST: C22.1, J3.4, R5.2, SW2.2 (B), U2.84 (NRESET); also elsewhere on the board
unnamed: FB4.2, J2.6 (Shield)
unnamed: LED4.2 (A), R20.2
unnamed: C27.1, U2.74 (LDO_CAP_1)
unnamed: C26.2, U2.161 (LDO_CAP_2)
unnamed: R10.2, R11.2, U3.6 (CLK)
unnamed: R12.2, R13.2, U3.5 (DI(IO0))
unnamed: R14.2, R15.2, U3.2 (DO(IO1))
unnamed: R16.2, R17.2, U3.3 (IO2)
unnamed: R18.2, R19.2, U3.7 (IO3)
unnamed: R8.2, R9.2, U3.1 (~CS)
unnamed: C31.1, U4.5 (NR\FB)
VDDA: C19.1, C20.1, C21.1, FB1.1, FB2.2, U2.168 (AVDD)
VREF: C13.1, C14.1, FB1.2, U2.169 (VREF)

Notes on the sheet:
Bypass Cap
LXT
QSPI0_SS
VBAT
QSPI0_MOSI1
SPIM_CLK
CLKO
VREF
QSPI0_MISO0
QSPI0_CLK
SPIM_SS
SPIM_MISO
SPIM_D2
QSPI0_MISO1
VDDIO
VDDA
HXT
SPIM_MOSI
RESET
SPIM_D3
SWD_DAT=PF.0 SWD_CLK=PF.1
QSPI0_MOSI0
